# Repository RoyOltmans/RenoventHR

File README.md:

# RenoventHR

All rights of the Mechenical ventelation system are owned by Renovent.

This is a reverse engeneered control device to remotely control and automate ventilation at home.

**Usage of this project is on your own risk.**

# Results

Some screenshot of the final endresult

Bottom view case

Side view case

Bottom view case

# Motivation

Connected RenoventHR Module to switch a mechanical ventilation heat recovery system from Renovent HR.

I was first inspired by a friend whom wanted to switch his mechanical ventilation. He has a Renovent setup and he could use a RF solution.
That started me thinking let’s try this myself, off course I have a different setup that’s a little more complicated because of the heat recovery.

After an evening of googling I found a site of an old classmate (what a small world) Ingmar Verheij. His journey is the same as mine, but he already solved it (https://www.ingmarverheij.com/bediening-wtw-altijd-op-de-verkeerde-plek/).

He posted a solution on git but did not finish a tutorial, so I thought I could solve this quickly. After approximately half a year I can say I finished reverse engineering the setup and build the whole project with a 3D printed case (still in backorder).

I refactored the code (separated code, minified web and altered some functionality so the interaction should work) to my taste and added a few configuration hacks. 
Changes made were approximately:
 - Minified HTML (minimize System footprint)
 - Further restructured and optimized code
 - Added manual config (personal taste)
 - Separated Core, Data, Interfacing and tools (not fully)
 - Removed intmode/pinmode (secondary in total)
 - Added/rebuild button, startup, filter functions
 - Restructured code
 - Changed MCP calls intMode to pinMode
 - Added manual WIFI configuration trough config file

Also, the reverse engineering of the electronics created a lot of issues. The original part list provided left out crucial info for the relays. I almost stopped because I couldn’t fix it, after measuring everything and re-checking (going back in the books) I discovered that the pictures of the relays on the site were not the correct voltage. The part list in the bottom are all the correct parts. Be careful with the rj12 jack, if you use a different form factor it maybe will not fit in the case (adjust the case according with fusion 360).

So, to let you wait further let’s go into the build.

# Building the code
The code needs to be compiled with preferably the Arduino IDE version 2.4.1 below the settings:

Set the compiler to use the right version 2.4.1 of nodemcu ESP firmware build tools. 

Set the correct settings for the HUZZAH board for uploading the compiled code.

I also added the working libraries, after a lot of juggling I figured these are the used standard libs:
https://github.com/RoyOltmans/RenoventHR/tree/master/lib

For flashing the HUZZAH via a normal usb cable use the correct sequence of buttons to get in program mode. If I remember correctly, GPIO0 must be low while booting: press and hold the reset button. press and hold the program button. release the reset button, the HUZZAH will boot in program mode.

# Case
 To build the case use the following STL files in this location https://github.com/RoyOltmans/RenoventHR/tree/master/bin/3D%20Models%20STL

I have also added the Fusion 360 (from autodesk https://www.autodesk.com/products/fusion-360/students-teachers-educators) file so you can edit the case (please do not judge my CAD skills).

You will need to get a DIN rail to mount the case on and if you prefer as I do a 5-volt din rail power source. 

See Mean Well DR-15-5 DIN-rail 5 V/DC2.4A 12W (https://s.click.aliexpress.com/e/mliRreY0)

# PCB's
To build the project firstly you need to order the PCB design via for example seeed studio, they can process eagle schema (in the repository).

The primary pcb:
https://github.com/RoyOltmans/RenoventHR/tree/master/pcb/EAGLE/RenoventHR%20v0.4

I ordered this board on https://www.seeedstudio.com/ was very happy with end result and the price.
To edit the board you will need Eagle (from autodesk https://www.autodesk.com/products/eagle/free-download) you can download this freely.

The double switch pcb:
https://github.com/RoyOltmans/RenoventHR/tree/master/pcb/Fritzing/Double%20Tactile%20Switch%20v0.3

I ordered this board directly via the tool, also very good service, price and quick (https://aisler.net/partners/fritzing).
To edit this board you will need fritzing you can download this for free (https://fritzing.org/home/).

# Pinlayout

Every connector PCB printed text should be horizontally aligned to number the pins, pin 1 itterating every pin plus 1 afterwards are the pin numbers.

LCD pinlayout
```
-----------------
JP_LCD PINS
Pin   1   2   3   4
      |   |   |   |
Pin  VCC GND SCL SDA
Connected to LCD 
-----------------
```
Switch Pinlayout
```
-----------------
JP_UP PINS:

Pin    1         2 
       |         |
Pin    -     Left Pin
JP_1 on DBL SW PCB
-----------------
JP_DOWN PINS
Pin    1         2 
       |         |
Pin Center Pin  Right Pin
JP_1 on DBL SW PCB
-----------------
```

WTW RJ12 connector
```
-----------------
JP_WTW PINS
  1     2    3    4      5    6
  |     |    |    |      |    |
White Black Red Green Yellow Blue
RJ12 Color coding
-----------------
```

# Tools
Personally, I solder with a soldering tip Pencil shape size 0.4 mm, this worked perfectly. 

Good tools are half of the work, new tip, good soldering paste (wire), magnifying glass etc.

# SMART-HUB - Home Assistant
For details on connecting to the HA, I suggest looking at the site of Ingmar https://www.ingmarverheij.com/built-smart-heat-recovery-system/

Be careful I changed the MQTT paths and these are accessible via the config file. I will repost them below:
```
/*-------------------MQTT topics-------------------*/
#define Gateway_Name "RenoventHR"
#define Base_Topic "home/"
#define MQTT_GetState_Topic Base_Topic Gateway_Name "/getWTWstate"
#define MQTT_State_Topic Base_Topic Gateway_Name "/wtwState"
#define MQTT_FilterState_Topic Base_Topic Gateway_Name "/changeFilter"
#define MQTT_SetState_Topic Base_Topic Gateway_Name "/setWTWstate"

#define MQTT_Standard_Topic Base_Topic Gateway_Name
```

After some tinkering I have decided to add a short totorial of the implementation in Home Assistant. Notice you will MQTT to get this fully operational.

Firstly I must give credits to **Ingmar Verheij** for researching the HA connectivity and the custom fan card support for HA by **finity69x2**, see his github for the original JS script *https://github.com/finity69x2/fan-control-entity-row*.

To start of, I am using a older version of **HA version 0.86.4**. *Be aware this can work differently on your version of HA.*

Firstly you will need to upload a javascript in to the `www` folder of the configuration root of home-assistant (your .yaml are also located here). If this folder does not exist create it. 

On linux you can do the following steps:
```
mkdir www
wget https://raw.githubusercontent.com/RoyOltmans/RenoventHR/master/code/Home%20Assistant/www/fan-control-entity-row.js
```

After you have done this on older version of HA you need to edit ui-lovelace.yaml (this does not work if you created a lovelace interactive version.

In ui-lovelace.yaml you will need to add the following below `resources`
```
  - url: /local/fan-control-entity-row.js
    type: js
```

If this does not work you can try to open the raw editor of lovelace and add the following at the top: 
```
resources:
  - type: js
    url: /local/fan-control-entity-row.js
```

Once your finished add a new file to the configuration root of home assistant. Use the follwoing command for that
```
wget https://raw.githubusercontent.com/RoyOltmans/RenoventHR/master/code/Home%20Assistant/fan.yaml
```

Onze you have done all these staps restart home assistant fully, this will reload and add the fan control of the WTW via MQTT.

Onze you have finished this you can add the following card to your lovelace dashboad. You can do this by toggling the editor and adding a card manualy via the lovelace configurator in HA.

```
entities:
  - customTheme: true
    entity: fan.wtw_mechanic_ventilation
    name: WTW Renovent HR
    type: 'custom:fan-control-entity-row'
    show_header_toggle: false
title: Mechinical Ventilation
type: entities
```

Below a screenshot of the card in Home Assistant.

Once you have added the fan you can control the fan levels via sesnors and automations you have designed yourself. Ingmar also described a way to add a notification for cleaning the filters. Please see his tutorial for further info.

# Configuration and Software
For configurations, you can follow the description on https://www.ingmarverheij.com/built-smart-heat-recovery-system/
The software as written by Ingmar is still operational, you can interact directly with the device. Or you can couple it through a smart hub via MQTT as described above.

Or edit the config.h file adding your personal configurations, below you will find the details of the config.h:
```
/*-------------------General----------------------*/
const char* Version = "0.5";

/*-------------------WIFI Settings----------------*/
String APssid = "SSID WIFI";
String APpassword = "PASSWORD WIFI";

/*-------------------MQTT Settings-------------------*/
String mqtt_user = "your_username"; // not compulsory only if your broker needs authentication
String mqtt_pass = "your_password"; // not compulsory only if your broker needs authentication
String mqtt_server = "MQTT SERVER NAME or IP";
long mqtt_port = strtol("1883",NULL,10);

/*-------------------MQTT topics-------------------*/
#define Gateway_Name "RenoventHR"
#define Base_Topic "home/"
#define MQTT_GetState_Topic Base_Topic Gateway_Name "/getWTWstate"
#define MQTT_State_Topic Base_Topic Gateway_Name "/wtwState"
#define MQTT_FilterState_Topic Base_Topic Gateway_Name "/changeFilter"
#define MQTT_SetState_Topic Base_Topic Gateway_Name "/setWTWstate"

#define MQTT_Standard_Topic Base_Topic Gateway_Name
```

# Part list

-  1x Miniature relay HJR-4102-L-05VDC-S-Z (order at Conrad (EU))
-  1x Miniature relay HJR1-2C-L-05VDC (order at Conrad (EU))
-  1x IC base 18 pins (order at Conrad (EU))
-  1x Jumper black open (Jumper zwart open) (order at Conrad (EU))
-  6x Carbon film resistance 0,5W 0411 330Ohm (Koolfilmweerstand 330Ω Axiaal bedraad 0411 0.5 W 5) (order at Conrad (EU))
-  1x Carbon film resistance 0,5W 0411 1KOhm (Koolfilmweerstand 1 kΩ Axiaal bedraad 0411 0.5 W 5 ) (order at Conrad (EU))
-  1x Bus, horizontal installation MUB1B5W 1 Port econ connect (order at Conrad (EU))
- 1x Würth Elektronik Male header (order at Conrad (EU))
- 1x Würth Elektronik Female header (standard) WR-PHD Total poles 10 grid size: 2.54 mm 61301011821 (order at Conrad (EU))
- 1x Microchip Technology MCP23008-E/P Interface-IC - I/O expansion POR I²C 1.7 MHz PDIP-18 (order at Conrad (EU))
-  2x Diotec BC547A Transistor (BJT) - discreet TO-92 1 NPN (order at Conrad (EU))
-  2x Diotec Si-rectifier diode 1N4004 DO-204AL 400 V 1 A (order at Conrad (EU))
- 1x Adafruit HUZZAH ESP8266 Breakout (https://www.adafruit.com/product/2471)
-  1x rj12 jack with cables and sleeve for case (https://s.click.aliexpress.com/e/ExAocZHe)
-  1x 0.96inch 128X64 Yellow Blue OLED Display Module (https://s.click.aliexpress.com/e/39m65cSM)
-  Dupont Wire Jumper Pin Header Connector (https://s.click.aliexpress.com/e/3WbYzW3I)
- Dupont Wires (https://s.click.aliexpress.com/e/KMFFxgfe)
-  A generic pushbutton (https://s.click.aliexpress.com/e/kaTmlRJw)

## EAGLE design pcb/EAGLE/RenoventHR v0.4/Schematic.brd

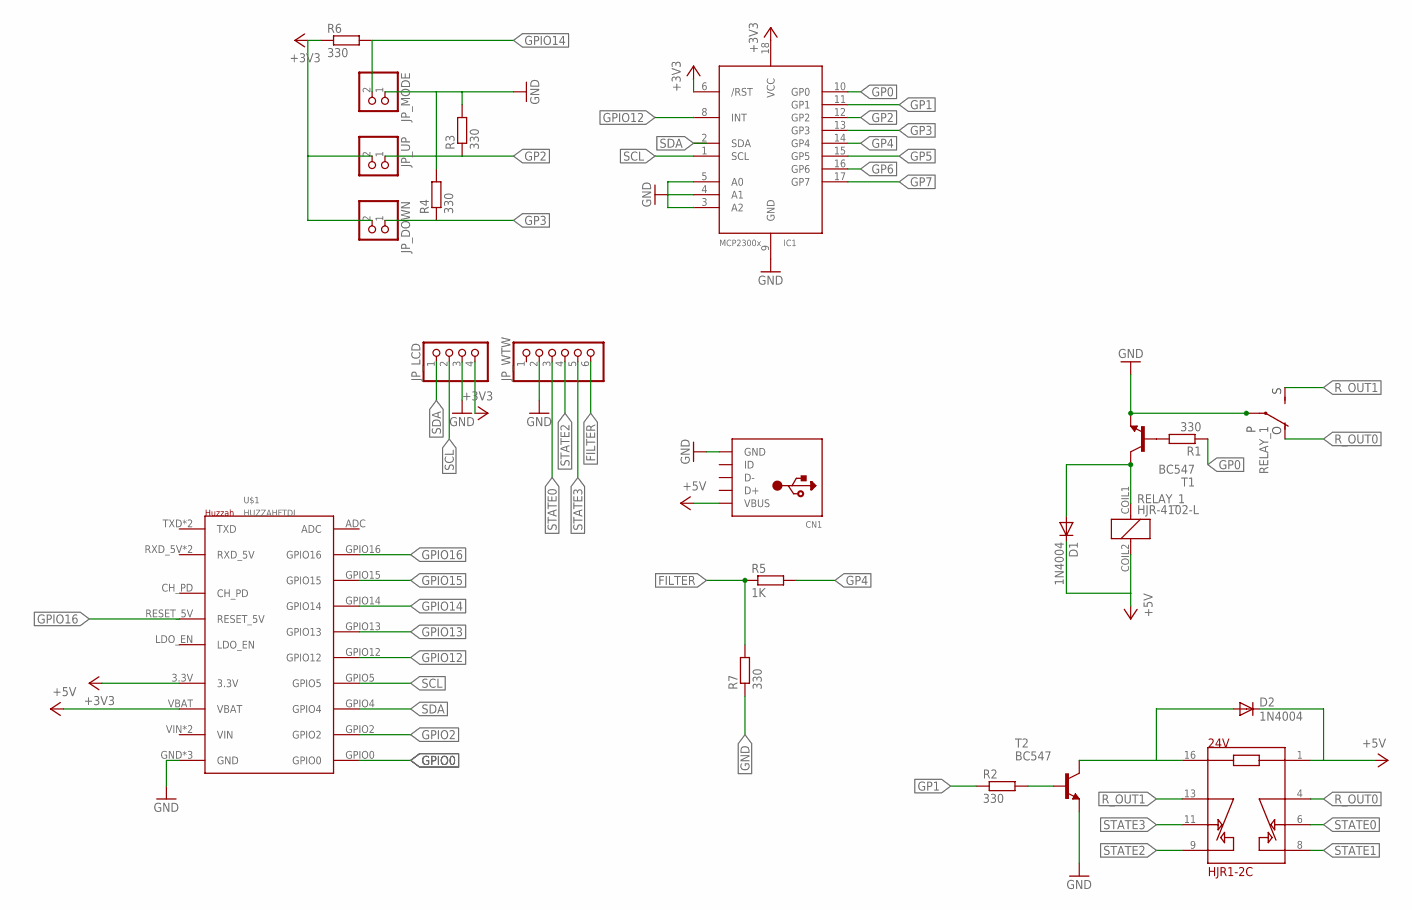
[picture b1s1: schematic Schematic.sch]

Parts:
CN1: USBTHM; USB-MINIB-THM
D1, D2: 1N4004; DO41-10
IC1: MCP23008/P; DIL18
JP_DOWN: PINHD-1X2; 1X02
JP_LCD: PINHD-1X4; 1X04
JP_MODE: PINHD-1X2; 1X02
JP_UP: PINHD-1X2; 1X02
JP_WTW: PINHD-1X6; 1X06
R1, R2, R3, R4, R6, R7: 330; 0207/10
R5: 1K; 0207/10
RELAY_1: HJR-4102-L; HJR4102
RELAY_2: HJR1-2C
T1, T2: BC547; TO92
U$1: HUZZAHFTDI; HUZZAH-FULL

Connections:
+3V3: IC1.6 (/RST), IC1.18 (VCC), JP_DOWN.2, JP_LCD.4, JP_UP.2, R6.1, U$1.3.3V
+5V: CN1.VBUS, D1.C, D2.C, RELAY_1.COIL2 (2), RELAY_2.1, U$1.VBAT
FILTER: JP_WTW.6, R5.1, R7.2
GND: CN1.GND, IC1.3 (A2), IC1.4 (A1), IC1.5 (A0), IC1.9 (GND), JP_LCD.3, JP_MODE.1, JP_WTW.2, R3.2, R4.2, R7.1, RELAY_1.CENTER1, RELAY_1.CENTER2 (P2), T1.1 (E), T2.1 (E), U$1.GND, U$1.GND2 (GND), U$1.GND3 (GND)
GP0: IC1.10 (GP0), R1.1
GP1: IC1.11 (GP1), R2.1
GP2: IC1.12 (GP2), JP_UP.1, R3.1
GP3: IC1.13 (GP3), JP_DOWN.1, R4.1
GP4: IC1.14 (GP4), R5.2
GP5: IC1.15 (GP5)
GP6: IC1.16 (GP6)
GP7: IC1.17 (GP7)
GPIO0: U$1.GPIO0
GPIO2: U$1.GPIO2
GPIO12: IC1.8 (INT), U$1.GPIO12
GPIO13: U$1.GPIO13
GPIO14: JP_MODE.2, R6.2, U$1.GPIO14
GPIO15: U$1.GPIO15
GPIO16: U$1.GPIO16, U$1.RESET_5V
unnamed: R1.2, T1.2 (B)
unnamed: R2.2, T2.2 (B)
R_OUT0: RELAY_1.CON2OPTION (O), RELAY_2.4
R_OUT1: RELAY_1.CON1DEFAULT (S), RELAY_2.13
SCL: IC1.1 (SCL), JP_LCD.2, U$1.GPIO5
SDA: IC1.2 (SDA), JP_LCD.1, U$1.GPIO4
STATE0: JP_WTW.3, RELAY_2.6
STATE1: RELAY_2.8
STATE2: JP_WTW.4, RELAY_2.9
STATE3: JP_WTW.5, RELAY_2.11
T1_RELAY1: D1.A, RELAY_1.COIL1 (1), T1.3 (C)
T2_RELAY2: D2.A, RELAY_2.16, T2.3 (C)

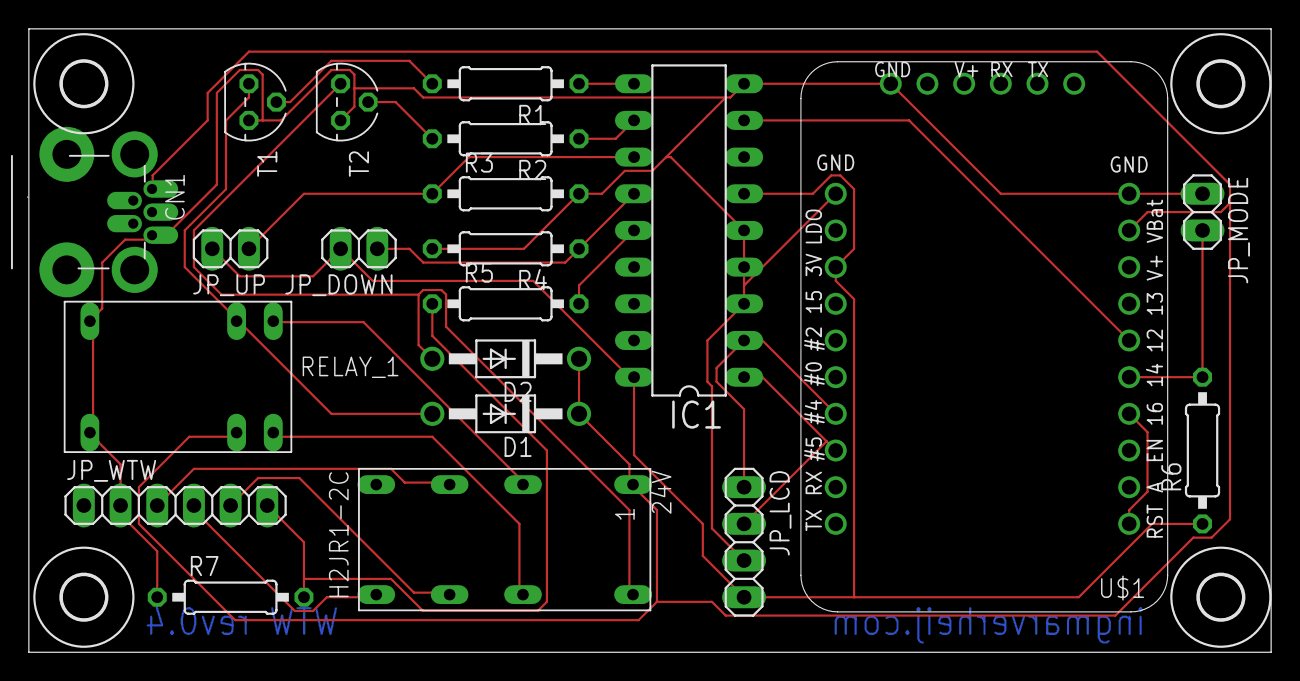
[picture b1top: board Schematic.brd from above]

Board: 2 copper layers, 86.0 x 43.2 mm, 25 parts (0 on the bottom side), 23 nets.

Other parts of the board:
U$2, U$3, U$4, U$5: 3,0
